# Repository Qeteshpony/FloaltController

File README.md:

# FLOALT Controller

[Schematics](https://qeteshpony.github.io/FloaltController/)

A custom, ESP32 based controller for the 30 x 90 cm IKEA FLOALT LED light panel. This probably works with other sizes of the panel as well but i can't test this since I don't own any of them. 

I created this since my original controller got fried by a thunderstorm and IKEA does not sell these anymore in Europe. 

As a side effect this allows way better control over the panel than the original controller which kept the light very bright even at lowest settings. The board is created with KiCad 7 and with production and assembly by JLCPCB in mind. Some components have to be purchased elsewhere and manually soldered. 

The controller is powered by a 24VDV 2.5A power supply, though 1.5A are enough if you never run both warm and cold white on full power at the same time. I use ESPHome with the included code to control this, which takes care of that automatically.

The included .stl file is a simple frame to glue the board to the back of the panel.

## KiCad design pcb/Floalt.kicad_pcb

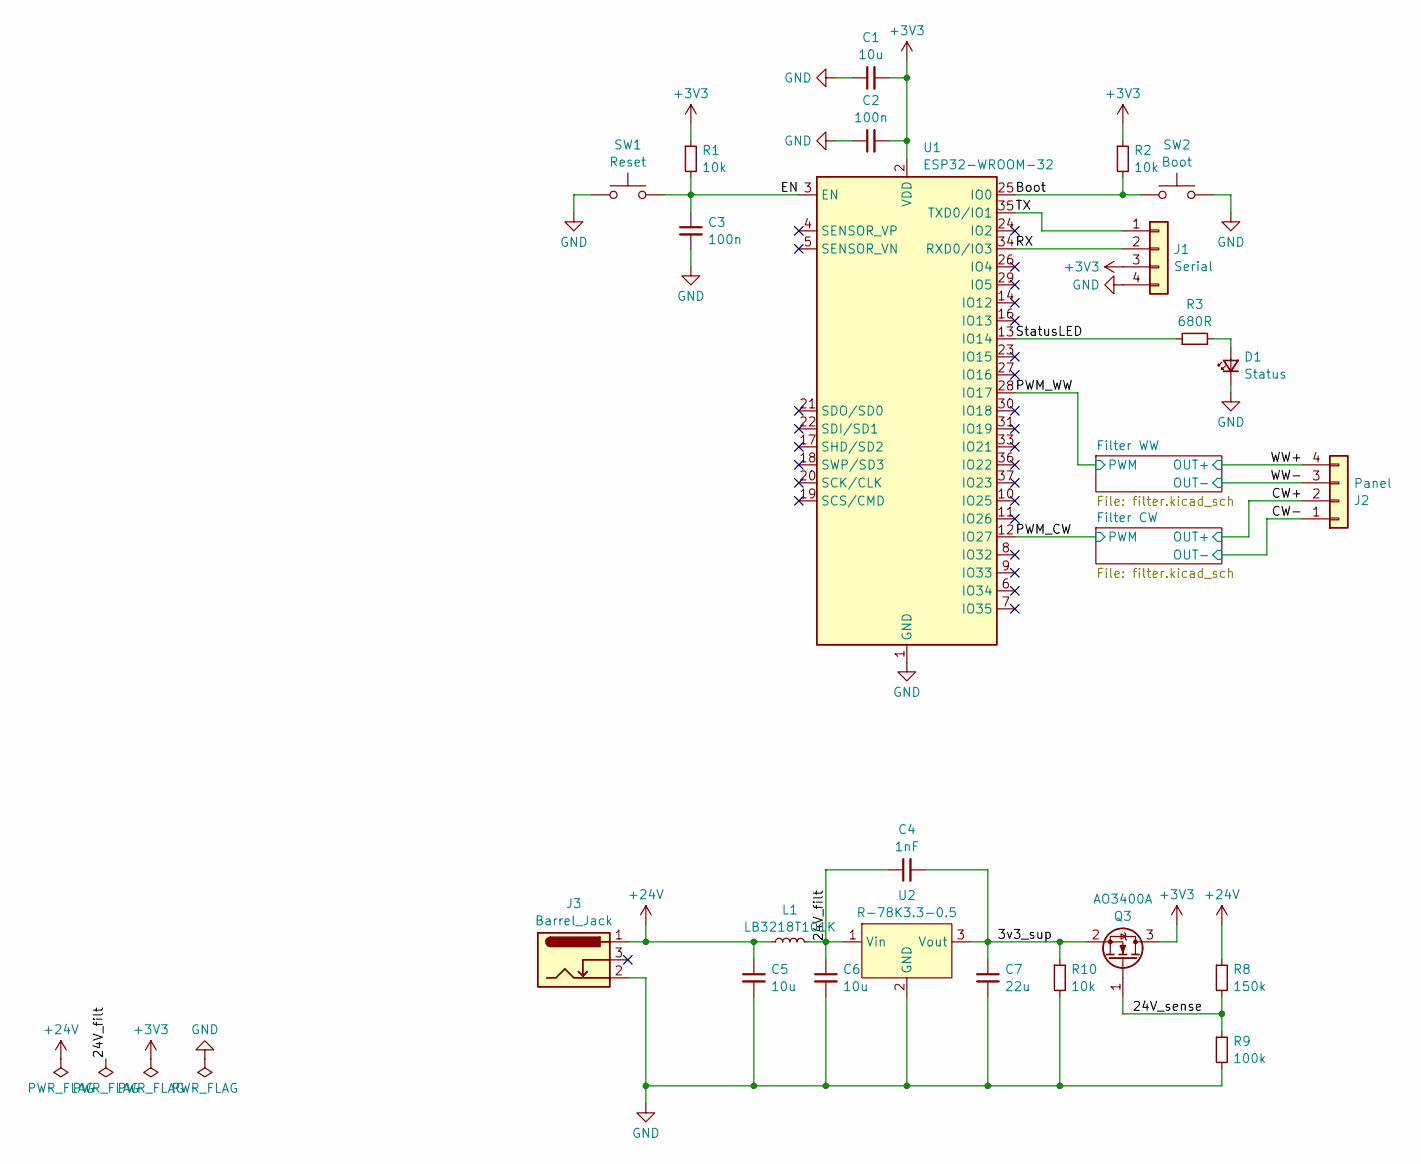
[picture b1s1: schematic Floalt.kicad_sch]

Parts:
C1: 10u; C_0402_1005Metric; LCSC C15525
C2, C3: 100n; C_0402_1005Metric; LCSC C307331
C4: 1nF; C_0402_1005Metric; LCSC C1523
C5, C6: 10u; C_1206_3216Metric; LCSC C13585
C7: 22u; C_1206_3216Metric; LCSC C12891
D1: Status; LED_0603_1608Metric; LCSC C2286
J1: Serial; PinSocket_1x04_P2.54mm_Vertical
J2: Panel; JST_VH_B4PS-VH_1x04_P3.96mm_Horizontal
J3: Barrel_Jack; BarrelJack_Horizontal
L1: LB3218T101K; L_1206_3216Metric_Pad1.22x1.90mm_HandSolder
Q3: AO3400A; SOT-23; LCSC C20917
R1, R2, R10: 10k; R_0402_1005Metric; LCSC C25744
R3: 680R; R_0402_1005Metric; LCSC C25130
R8: 150k; R_0402_1005Metric; LCSC C25755
R9: 100k; R_0402_1005Metric; LCSC C25741
SW1: Reset; SW_Push_1P1T_XKB_TS-1187A; LCSC C318884
SW2: Boot; SW_Push_1P1T_XKB_TS-1187A; LCSC C318884
U1: ESP32-WROOM-32
U2: R-78K3.3-0.5; LME78_1.0-Series

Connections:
+3V3: C1.2, C2.2, J1.3, Q3.3 (D), R1.1, R2.1, U1.2 (VDD)
+24V: C5.1, J3.1, L1.1, R8.1; also elsewhere on the board
/3v3_sup: C4.2, C7.1, Q3.2 (S), R10.1, U2.3 (Vout)
/24V_filt: C4.1, C6.1, L1.2, U2.1 (Vin)
/24V_sense: Q3.1 (G), R8.2, R9.1
/Boot: R2.2, SW2.1, U1.25 (IO0)
/CW+: J2.2; also elsewhere on the board
/CW-: J2.1; also elsewhere on the board
/EN: C3.1, R1.2, SW1.2, U1.3 (EN)
/PWM_CW: U1.12 (IO27); also elsewhere on the board
/PWM_WW: U1.28 (IO17); also elsewhere on the board
/RX: J1.2, U1.34 (RXD0/IO3)
/StatusLED: R3.1, U1.13 (IO14)
/TX: J1.1, U1.35 (TXD0/IO1)
/WW+: J2.4; also elsewhere on the board
/WW-: J2.3; also elsewhere on the board
GND: C1.1, C2.1, C3.2, C5.2, C6.2, C7.2, D1.1 (K), J1.4, J3.2, R9.2, R10.2, SW1.1, SW2.2, U1.1 (GND), U1.15 (GND), U1.38 (GND), U1.39 (GND), U2.2 (GND); also elsewhere on the board
unnamed: D1.2 (A), R3.2

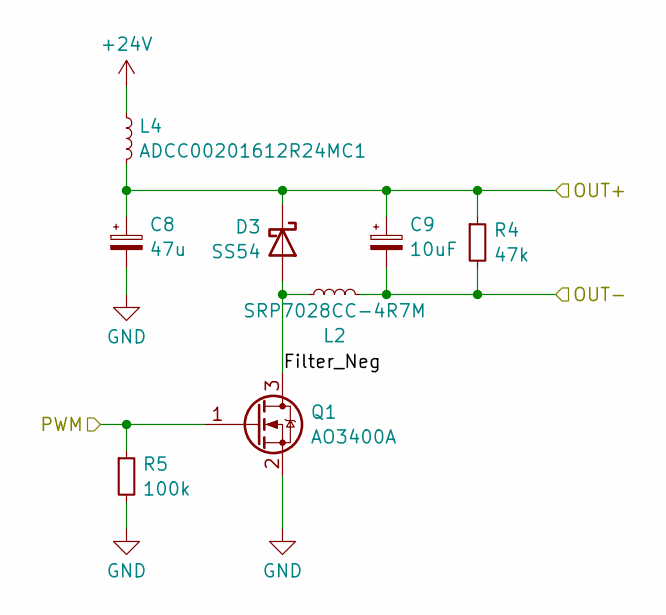
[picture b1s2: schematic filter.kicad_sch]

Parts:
C8: 47u; CP_Elec_6.3x5.8
C9: 10uF; CP_Elec_5x5.8
D3: SS54; D_SMA; LCSC C22452
L2: SRP7028CC-4R7M; L_Bourns_SRP7028A_7.3x6.6mm
L4: ADCC00201612R24MC1; L_0805_2012Metric_Pad1.15x1.40mm_HandSolder
Q1: AO3400A; SOT-23; LCSC C20917
R4: 47k; R_0805_2012Metric; LCSC C17713
R5: 100k; R_0402_1005Metric; LCSC C25741

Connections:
+24V: L4.1; also elsewhere on the board
/CW+: C8.1, C9.1, D3.1 (K), L4.2, R4.1; also elsewhere on the board
/CW-: C9.2, L2.2, R4.2; also elsewhere on the board
/Filter CW/Filter_Neg: D3.2 (A), L2.1, Q1.3 (D)
/PWM_CW: Q1.1 (G), R5.1; also elsewhere on the board
GND: C8.2, Q1.2 (S), R5.2; also elsewhere on the board

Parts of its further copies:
C10: 47u; CP_Elec_6.3x5.8
C11: 10uF; CP_Elec_5x5.8
D4: SS54; D_SMA; LCSC C22452
L3: SRP7028CC-4R7M; L_Bourns_SRP7028A_7.3x6.6mm
L5: ADCC00201612R24MC1; L_0805_2012Metric_Pad1.15x1.40mm_HandSolder
Q2: AO3400A; SOT-23; LCSC C20917
R6: 47k; R_0805_2012Metric; LCSC C17713
R7: 100k; R_0402_1005Metric; LCSC C25741

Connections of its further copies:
+24V: L5.1; also elsewhere on the board
/Filter WW/Filter_Neg: D4.2 (A), L3.1, Q2.3 (D)
/PWM_WW: Q2.1 (G), R7.1; also elsewhere on the board
/WW+: C10.1, C11.1, D4.1 (K), L5.2, R6.1; also elsewhere on the board
/WW-: C11.2, L3.2, R6.2; also elsewhere on the board
GND: C10.2, Q2.2 (S), R7.2; also elsewhere on the board

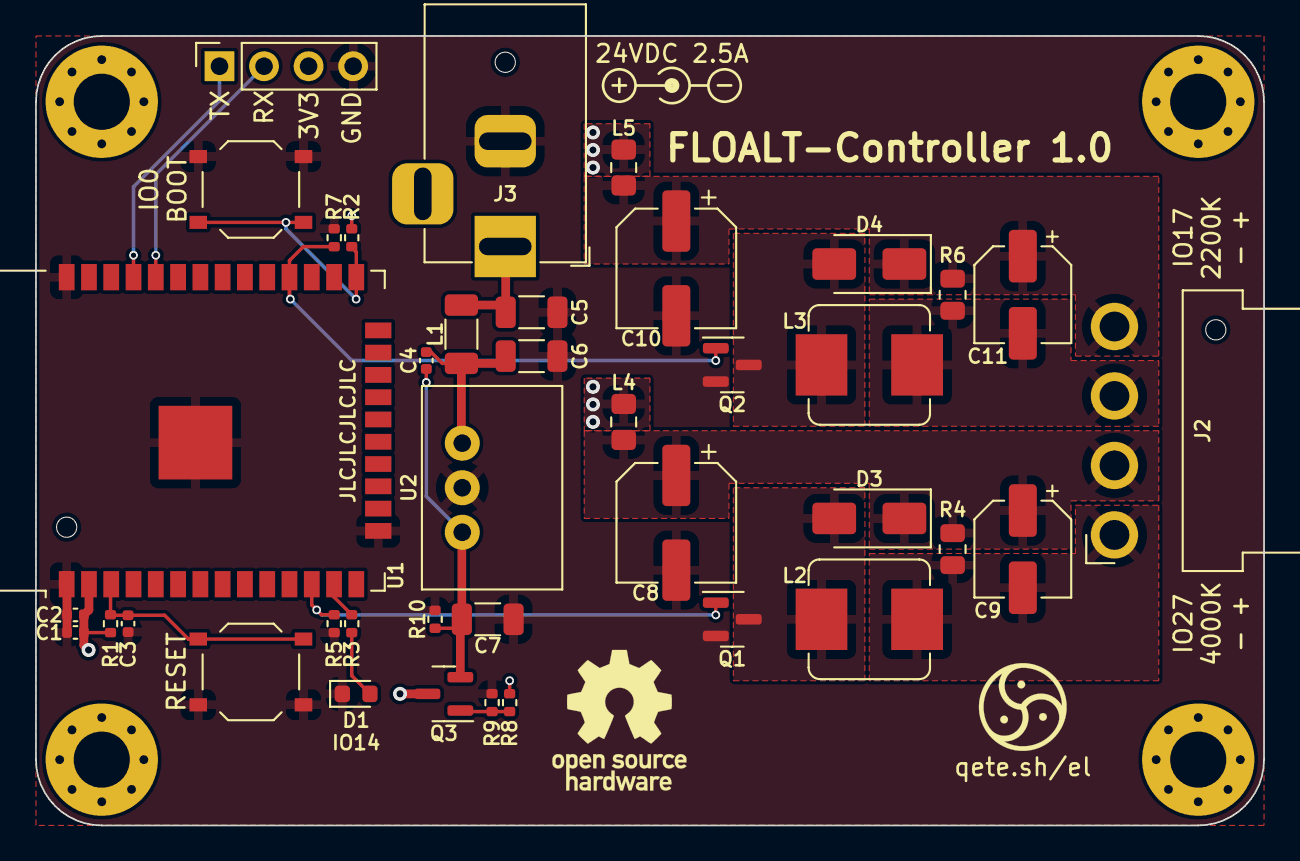
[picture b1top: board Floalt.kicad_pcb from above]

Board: 2 copper layers, 70.0 x 45.0 mm, 39 parts (0 on the bottom side), 20 nets.

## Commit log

2023-12-07 feat: initial commit
2023-12-07 feat: add ESPHome code
2023-12-07 docs: add README
2023-12-07 chore(main): release 1.0.0
2023-12-07 docs: update README
2024-08-29 ci: remove dependency between jobs
